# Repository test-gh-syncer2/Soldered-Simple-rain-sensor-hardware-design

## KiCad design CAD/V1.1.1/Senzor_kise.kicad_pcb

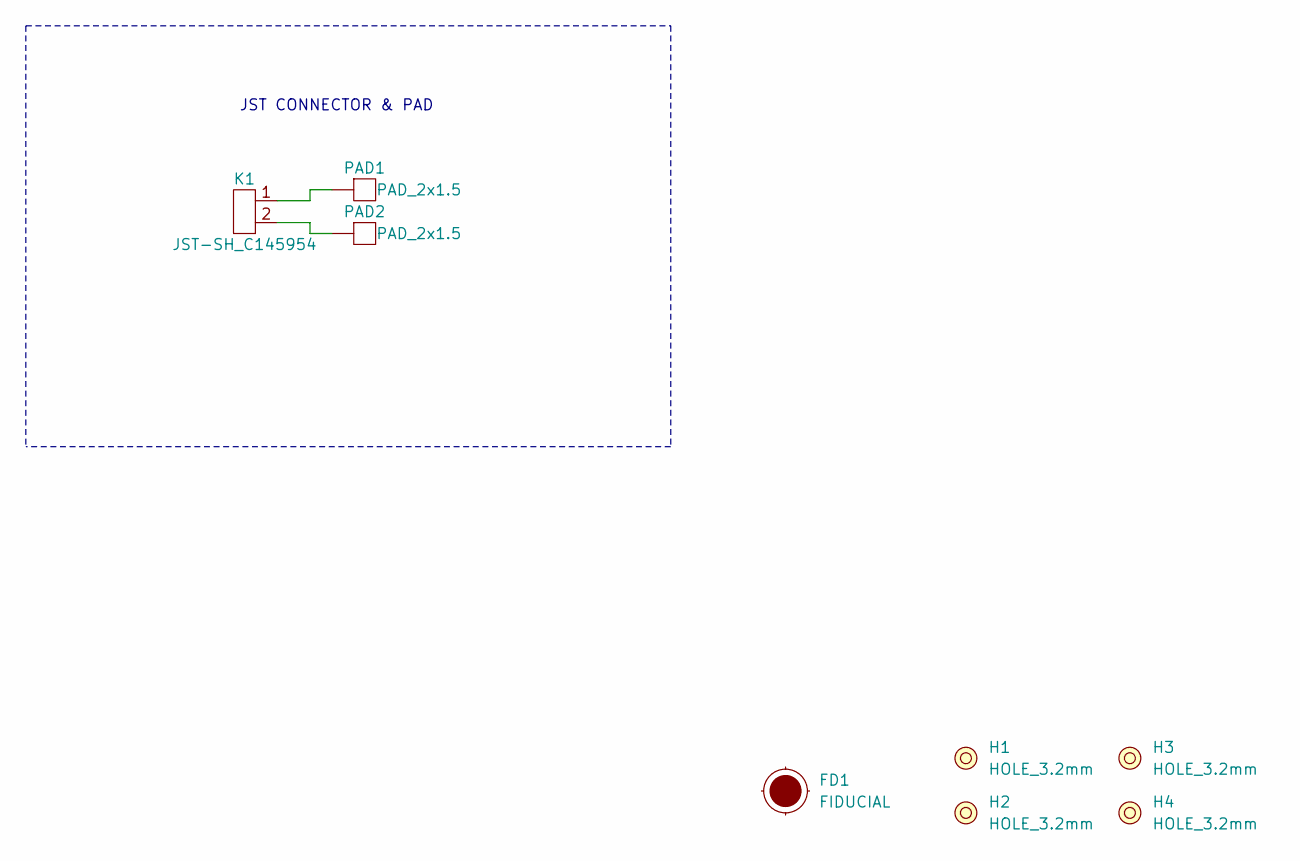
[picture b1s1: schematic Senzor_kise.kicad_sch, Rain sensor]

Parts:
FD1: FIDUCIAL; FIDUCIAL_23
H1, H2, H3, H4: HOLE_3.2mm
K1: JST-SH_C145954; JST-SH_2pin_1mm_C145954
PAD1, PAD2: PAD_2x1.5

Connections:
unnamed: K1.1, PAD1.1
unnamed: K1.2, PAD2.1

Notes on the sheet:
JST CONNECTOR & PAD

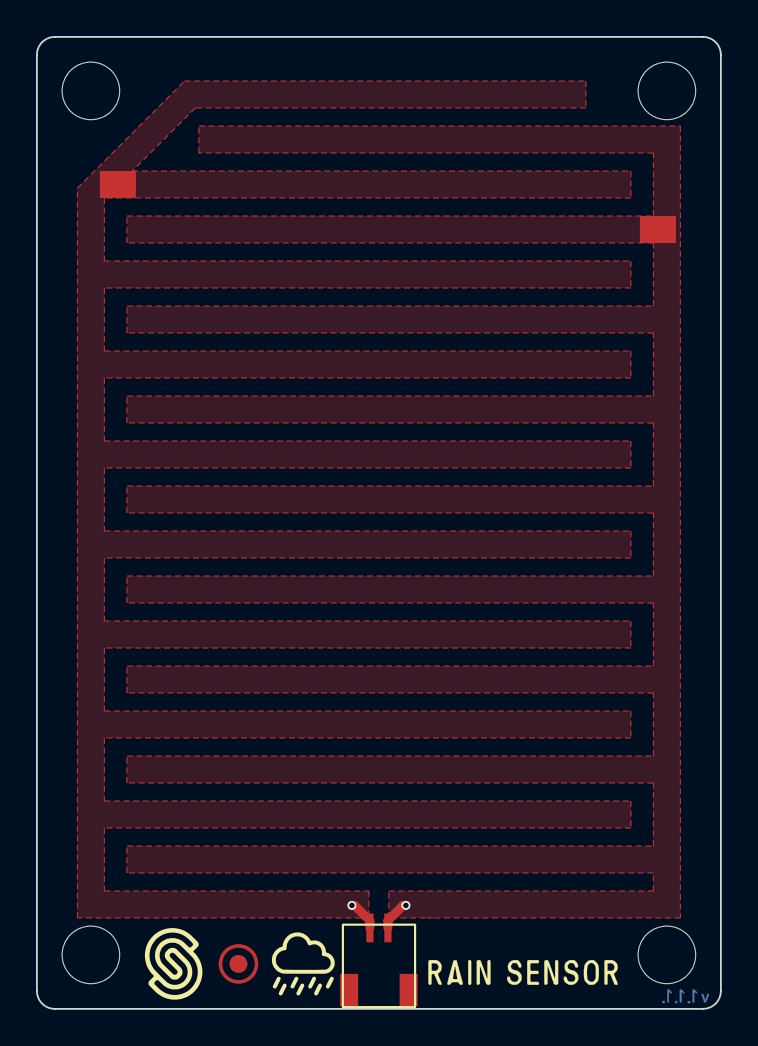
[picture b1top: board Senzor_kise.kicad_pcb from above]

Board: 2 copper layers, 38.0 x 54.0 mm, 8 parts (0 on the bottom side), 2 nets.

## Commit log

2021-09-23 Syncing to git
2021-09-23 Updating open source files.
